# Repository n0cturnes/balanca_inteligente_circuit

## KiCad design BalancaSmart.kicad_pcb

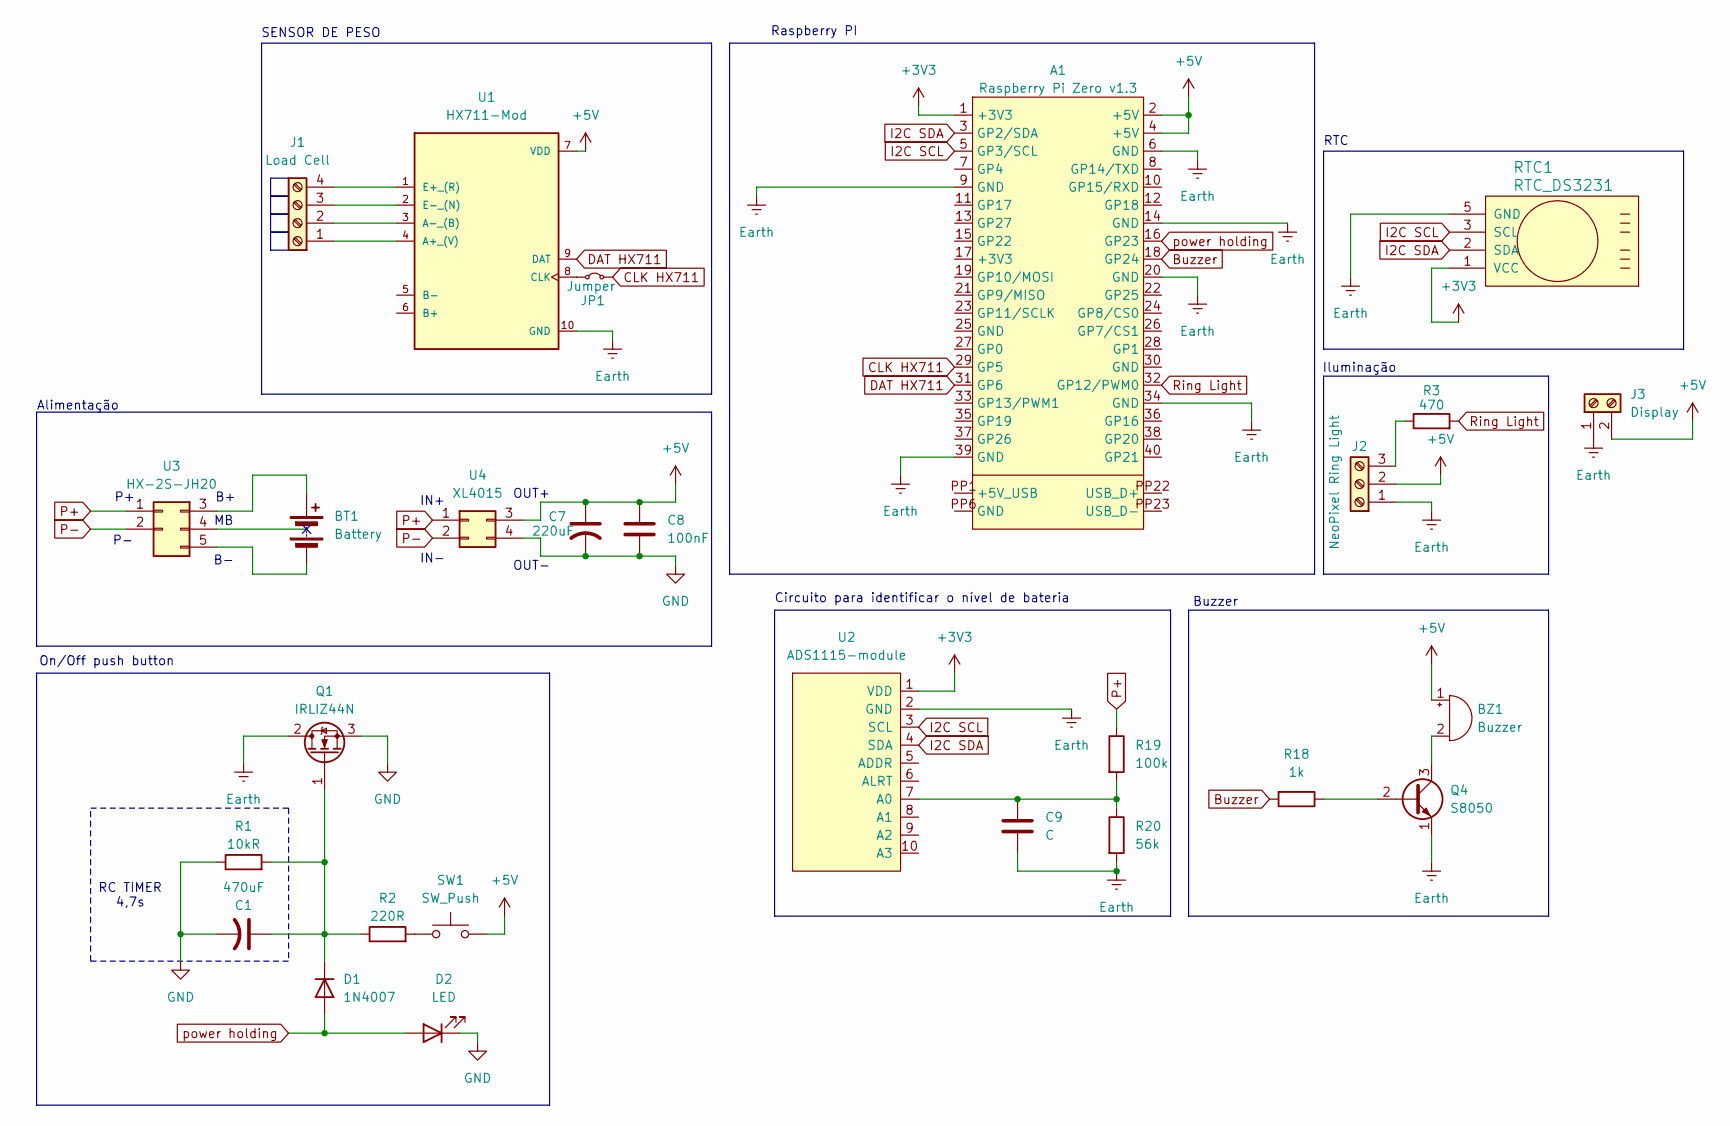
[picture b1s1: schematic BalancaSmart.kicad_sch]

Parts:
A1: Raspberry Pi Zero v1.3; Raspberry_Pi_Zero_Socketed_THT_FaceDown_MountingHoles
BT1: Battery
BZ1: Buzzer; MagneticBuzzer_PUI_AT-0927-TT-6-R
C1: 470uF; C_Radial_D6.3mm_H7.0mm_P2.50mm
C7: 220uF; C_Radial_D6.3mm_H7.0mm_P2.50mm
C8: 100nF; C_Disc_D5.0mm_W2.5mm_P2.50mm
C9: C; C_Radial_D6.3mm_H7.0mm_P2.50mm
D1: 1N4007; D_DO-41_SOD81_P10.16mm_Horizontal
D2: LED; LED_D5.0mm
J1: Load Cell; TerminalBlock_MaiXu_MX126-5.0-04P_1x04_P5.00mm
J2: NeoPixel Ring Light; TerminalBlock_MaiXu_MX126-5.0-03P_1x03_P5.00mm
J3: Display; TerminalBlock_MaiXu_MX126-5.0-02P_1x02_P5.00mm
JP1: Jumper; R_Axial_DIN0207_L6.3mm_D2.5mm_P10.16mm_Horizontal
Q1: IRLIZ44N; TO-220F-3_Vertical
Q4: S8050; PinHeader_1x03_P2.54mm_Vertical
R1: 10kR; R_Axial_DIN0204_L3.6mm_D1.6mm_P7.62mm_Horizontal
R2: 220R; R_Axial_DIN0207_L6.3mm_D2.5mm_P10.16mm_Horizontal
R3: 470; R_Axial_DIN0204_L3.6mm_D1.6mm_P7.62mm_Horizontal
R18: 1k; R_Axial_DIN0207_L6.3mm_D2.5mm_P10.16mm_Horizontal
R19: 100k; R_Axial_DIN0204_L3.6mm_D1.6mm_P7.62mm_Horizontal
R20: 56k; R_Axial_DIN0204_L3.6mm_D1.6mm_P7.62mm_Horizontal
RTC1: RTC_DS3231; PinHeader_1x05_P2.54mm_Vertical
SW1: SW_Push; TerminalBlock_MaiXu_MX126-5.0-02P_1x02_P5.00mm
U1: HX711-Mod; HX711_module
U2: ADS1115-module; ADS1115 Module
U3: HX-2S-JH20; TerminalBlock_MaiXu_MX126-5.0-02P_1x02_P5.00mm
U4: XL4015; TerminalBlock_MaiXu_MX126-5.0-04P_1x04_P5.00mm

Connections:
+3V3: A1.1 (+3V3), RTC1.1 (VCC), U2.1 (VDD)
+5V: A1.2 (+5V), A1.4 (+5V), BZ1.1 (+), C7.1, C8.1, J2.2, J3.2, SW1.2, U1.7 (VDD), U4.3
Buzzer: A1.18 (GP24), R18.2
CLK HX711: A1.29 (GP5), JP1.2 (B)
DAT HX711: A1.31 (GP6), U1.9 (DAT)
Earth: A1.6 (GND), A1.9 (GND), A1.14 (GND), A1.20 (GND), A1.34 (GND), A1.39 (GND), C9.2, J2.1, J3.1, Q1.2 (D), Q4.1 (E), R20.2, RTC1.5 (GND), U1.10 (GND), U2.2 (GND)
GND: C1.2, C7.2, C8.2, D2.1 (K), Q1.3 (S), R1.1, U4.4
I2C SCL: A1.5 (GP3/SCL), RTC1.3 (SCL), U2.3 (SCL)
I2C SDA: A1.3 (GP2/SDA), RTC1.2 (SDA), U2.4 (SDA)
unnamed: BT1.1 (+), U3.3 (B+)
unnamed: BT1.2 (-), U3.5 (B-)
unnamed: BZ1.2 (-), Q4.3 (C)
unnamed: C1.1, D1.1 (K), Q1.1 (G), R1.2, R2.1
unnamed: J1.1, U1.4 (A+_(V))
unnamed: J1.2, U1.3 (A-_(B))
unnamed: J1.3, U1.2 (E-_(N))
unnamed: J1.4, U1.1 (E+_(R))
unnamed: J2.3, R3.1
unnamed: JP1.1 (A), U1.8 (CLK)
unnamed: Q4.2 (B), R18.1
unnamed: R2.2, SW1.1
unnamed: C9.1, R19.2, R20.1, U2.7 (A0)
P+: R19.1, U3.1 (P+), U4.1
P-: U3.2 (P-), U4.2
Ring Light: A1.32 (GP12/PWM0), R3.2
power holding: A1.16 (GP23), D1.2 (A), D2.2 (A)

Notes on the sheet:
RTC
On/Off push button
OUT+
Raspberry PI
SENSOR DE PESO
IN+
IN-
Iluminação
Alimentação
Circuito para identificar o nível de bateria
Buzzer
OUT-
RC TIMER 4,7s

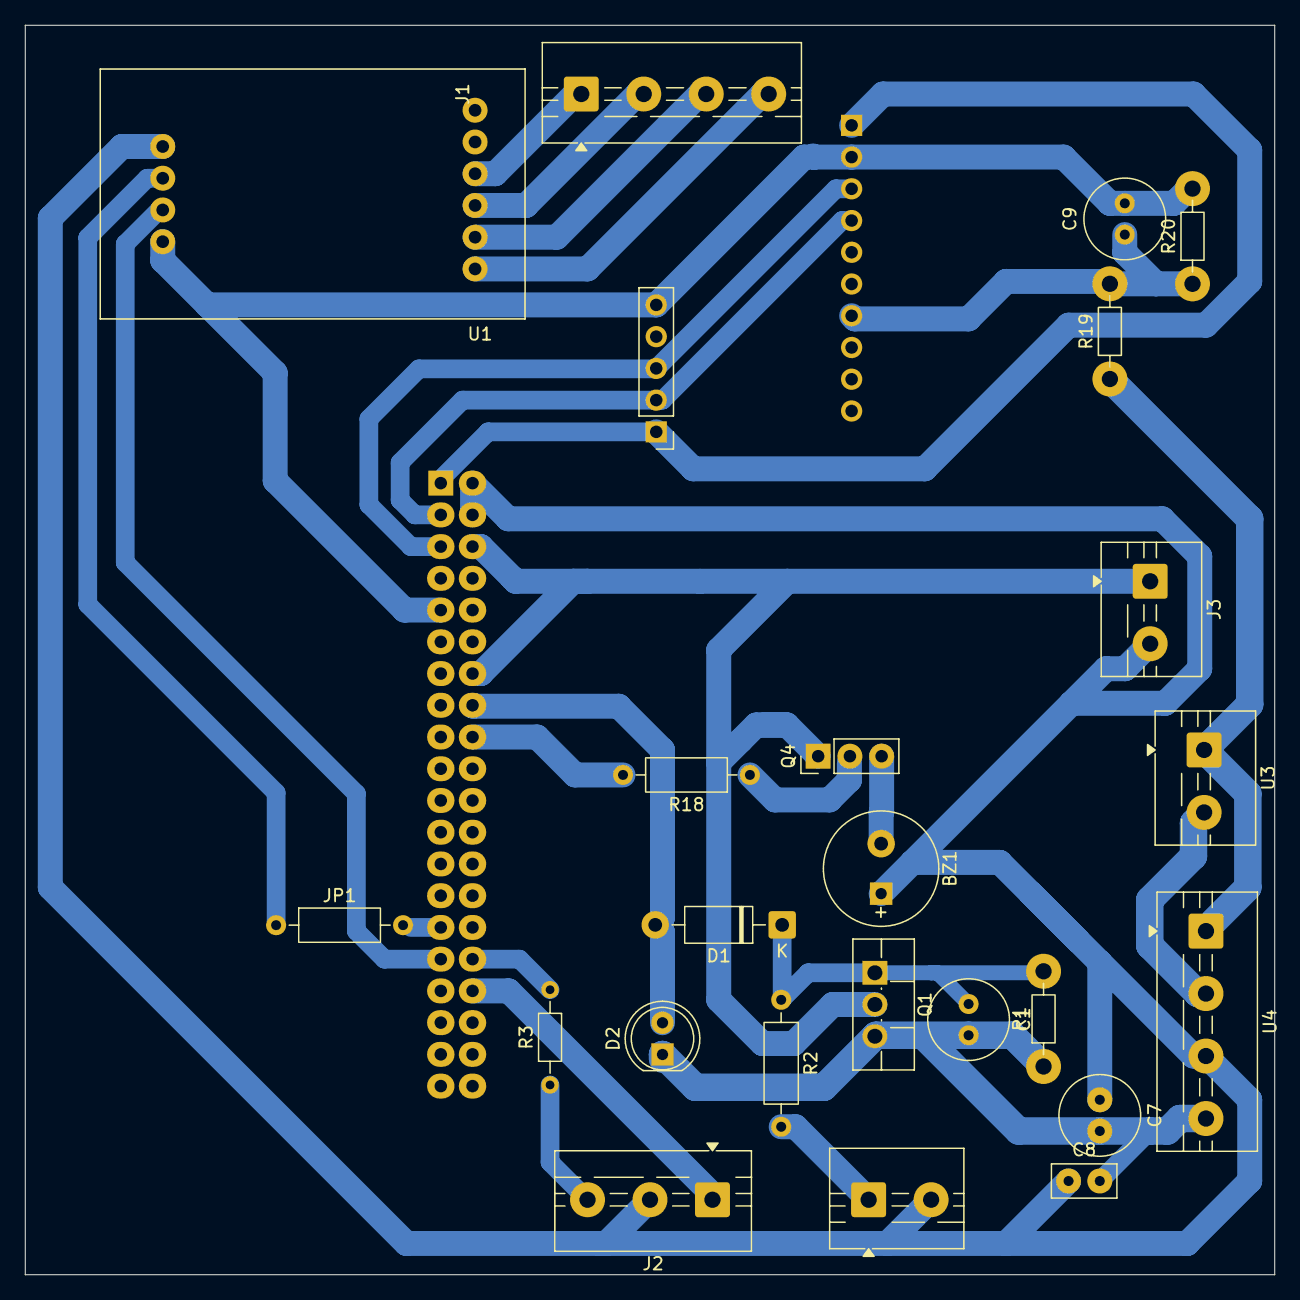
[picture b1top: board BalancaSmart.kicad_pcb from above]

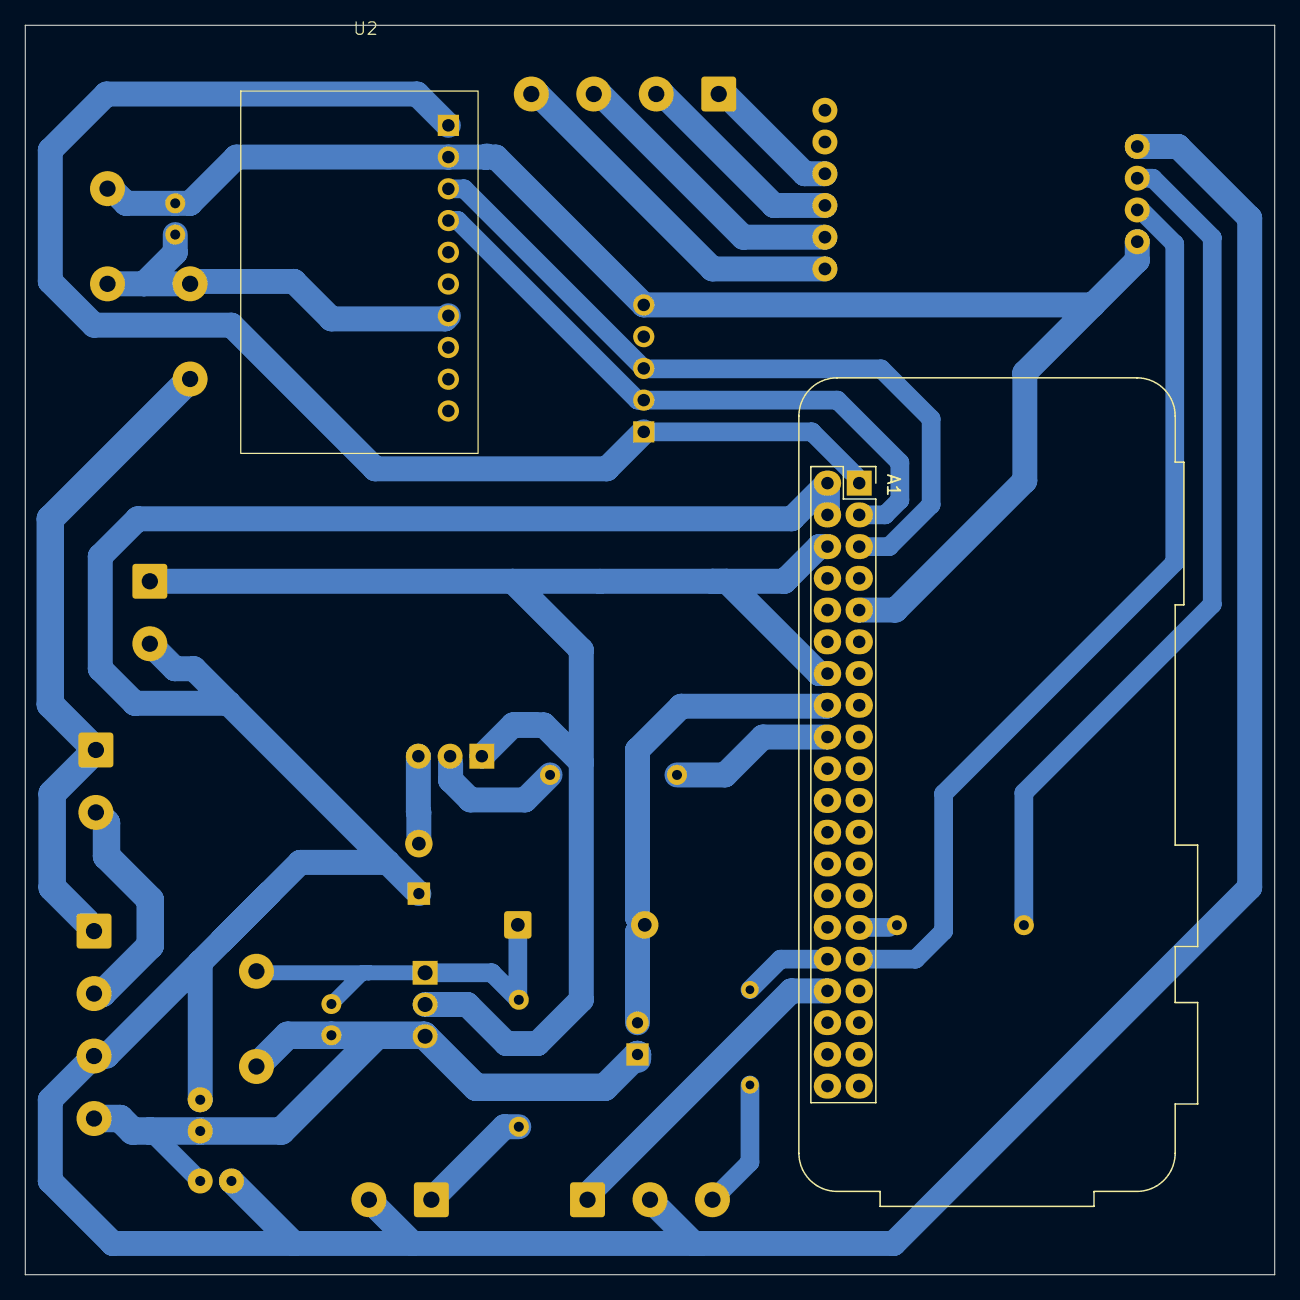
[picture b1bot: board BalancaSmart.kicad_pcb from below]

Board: 2 copper layers, 100.0 x 100.0 mm, 26 parts (2 on the bottom side), 24 nets.

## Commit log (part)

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2026-05-18 esquemático ok, inicio do design da pcb
2026-05-18 Create .gitignore for KiCad project
    Add .gitignore for KiCad project files and temporary files
2026-05-18 adicionado footprint do ADS1115, continuação do desenvolvimento do layout da pcb
2026-05-19 designação de footprints
2026-05-21 layout do circuito dos leds
2026-05-28 continuação do layout da PCB e designação de footprints
2026-05-29 continuação pcb
2026-05-30 layout PCB finalizado
2026-05-30 Arquivos para impressão para realizar termotransferência
